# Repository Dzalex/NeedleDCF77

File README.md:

# NeedleDCF77
## General idea
This project is a clock that shows time using three analog meters (with needle) for hours, minutes and seconds, and a VFD for the date. The time reference is the [DCF77](https://en.wikipedia.org/wiki/DCF77) longwave signal, receivable across most of Europe — no manual time setting, no NTP, no RTC drift correction needed beyond the daily resync.

### Assembled clock

## Hardware
  - Main microcontroller: *STM32L051C8T6*
  - Power supply built around Analog Devices' *LTC3558* (Li-Po charge + regulation)
  - DCF77 receiver module: *EB6180B1COB77K5A1*
  - [VFD](https://en.wikipedia.org/wiki/Vacuum_fluorescent_display) for the date — a salvaged Itron FG95A
    - Driver: PT6312
    - Filament driver: LM4871 (alternative: LM9022)
    - Inverting regulator: LT1617
  - Analog meters, repurposed as needle displays:
    - Simpson 60 x 60 mm — hours
    - 85C1-A — minutes
    - 91C4 — seconds
  - Enclosure: wooden box, 20 x 10 x 6 cm
  - Battery: Panasonic 18650B

Schematic and PCB are designed in *KiCad* — see [`hardware/NeedleDCF77`](hardware/NeedleDCF77), including a rendered [schematic PDF](hardware/NeedleDCF77/DCF77Needle_schematic.pdf).

## Software
Firmware lives in [`sw/STM32CubeIDE_Project`](sw/STM32CubeIDE_Project), written in C on top of **FreeRTOS**, developed with **STM32CubeIDE** / STM32CubeMX and built with **CMake**.

### Layout
  - `Core/` — STM32CubeMX-generated init code, HAL configuration, and the FreeRTOS task wiring (`freertos.c`).
  - `BSP/` — hardware-facing drivers: DCF77 signal capture (`dcf77.c`), needle PWM output (`needle.c`), VFD control (`vfd.c`), battery/power management (`powerManagement.c`).
  - `App/` — hardware-independent application logic: DCF77 frame decoding (`dcf77Decoding.c`), needle/VFD interface state (`interface.c`).

### What it does
  - `StartDCF77Task` samples the DCF77 signal, decodes the time/date frame, validates it (parity + range/sanity checks) and syncs the RTC once per day (2 AM) or on button press.
  - `StartInterfaceTask` drives the needles from RTC time every second and shows the date on the VFD on button press; the display is suspended while a sync is in progress.
  - FreeRTOS tickless idle is enabled (`Core/Inc/FreeRTOSConfig.h`) so the MCU sleeps between scheduled work; `powerManagement.c` separately handles battery voltage readout and Li-Po charger control (LTC3558).

### Building the firmware
```sh
cmake --preset Debug      # or Release
cmake --build build/Debug
```
The project can also be opened directly in STM32CubeIDE.

### Running the unit tests
DCF77 frame decoding (`App/Src/dcf77Decoding.c`) is unit-tested on the host with [Unity](sw/STM32CubeIDE_Project/test/subprojects/unity), independent of any HAL/hardware dependency:
```sh
cd sw/STM32CubeIDE_Project/test
meson setup build
meson test -C build
```

## Improvements to come
  - Algorithm to index the current bit by time elapsed from the minute mark, so a missed/noisy pulse doesn't throw off subsequent bits, and to retain good bits from a previous sample.
  - Improve battery monitoring and charging. Alerting user on that regard.

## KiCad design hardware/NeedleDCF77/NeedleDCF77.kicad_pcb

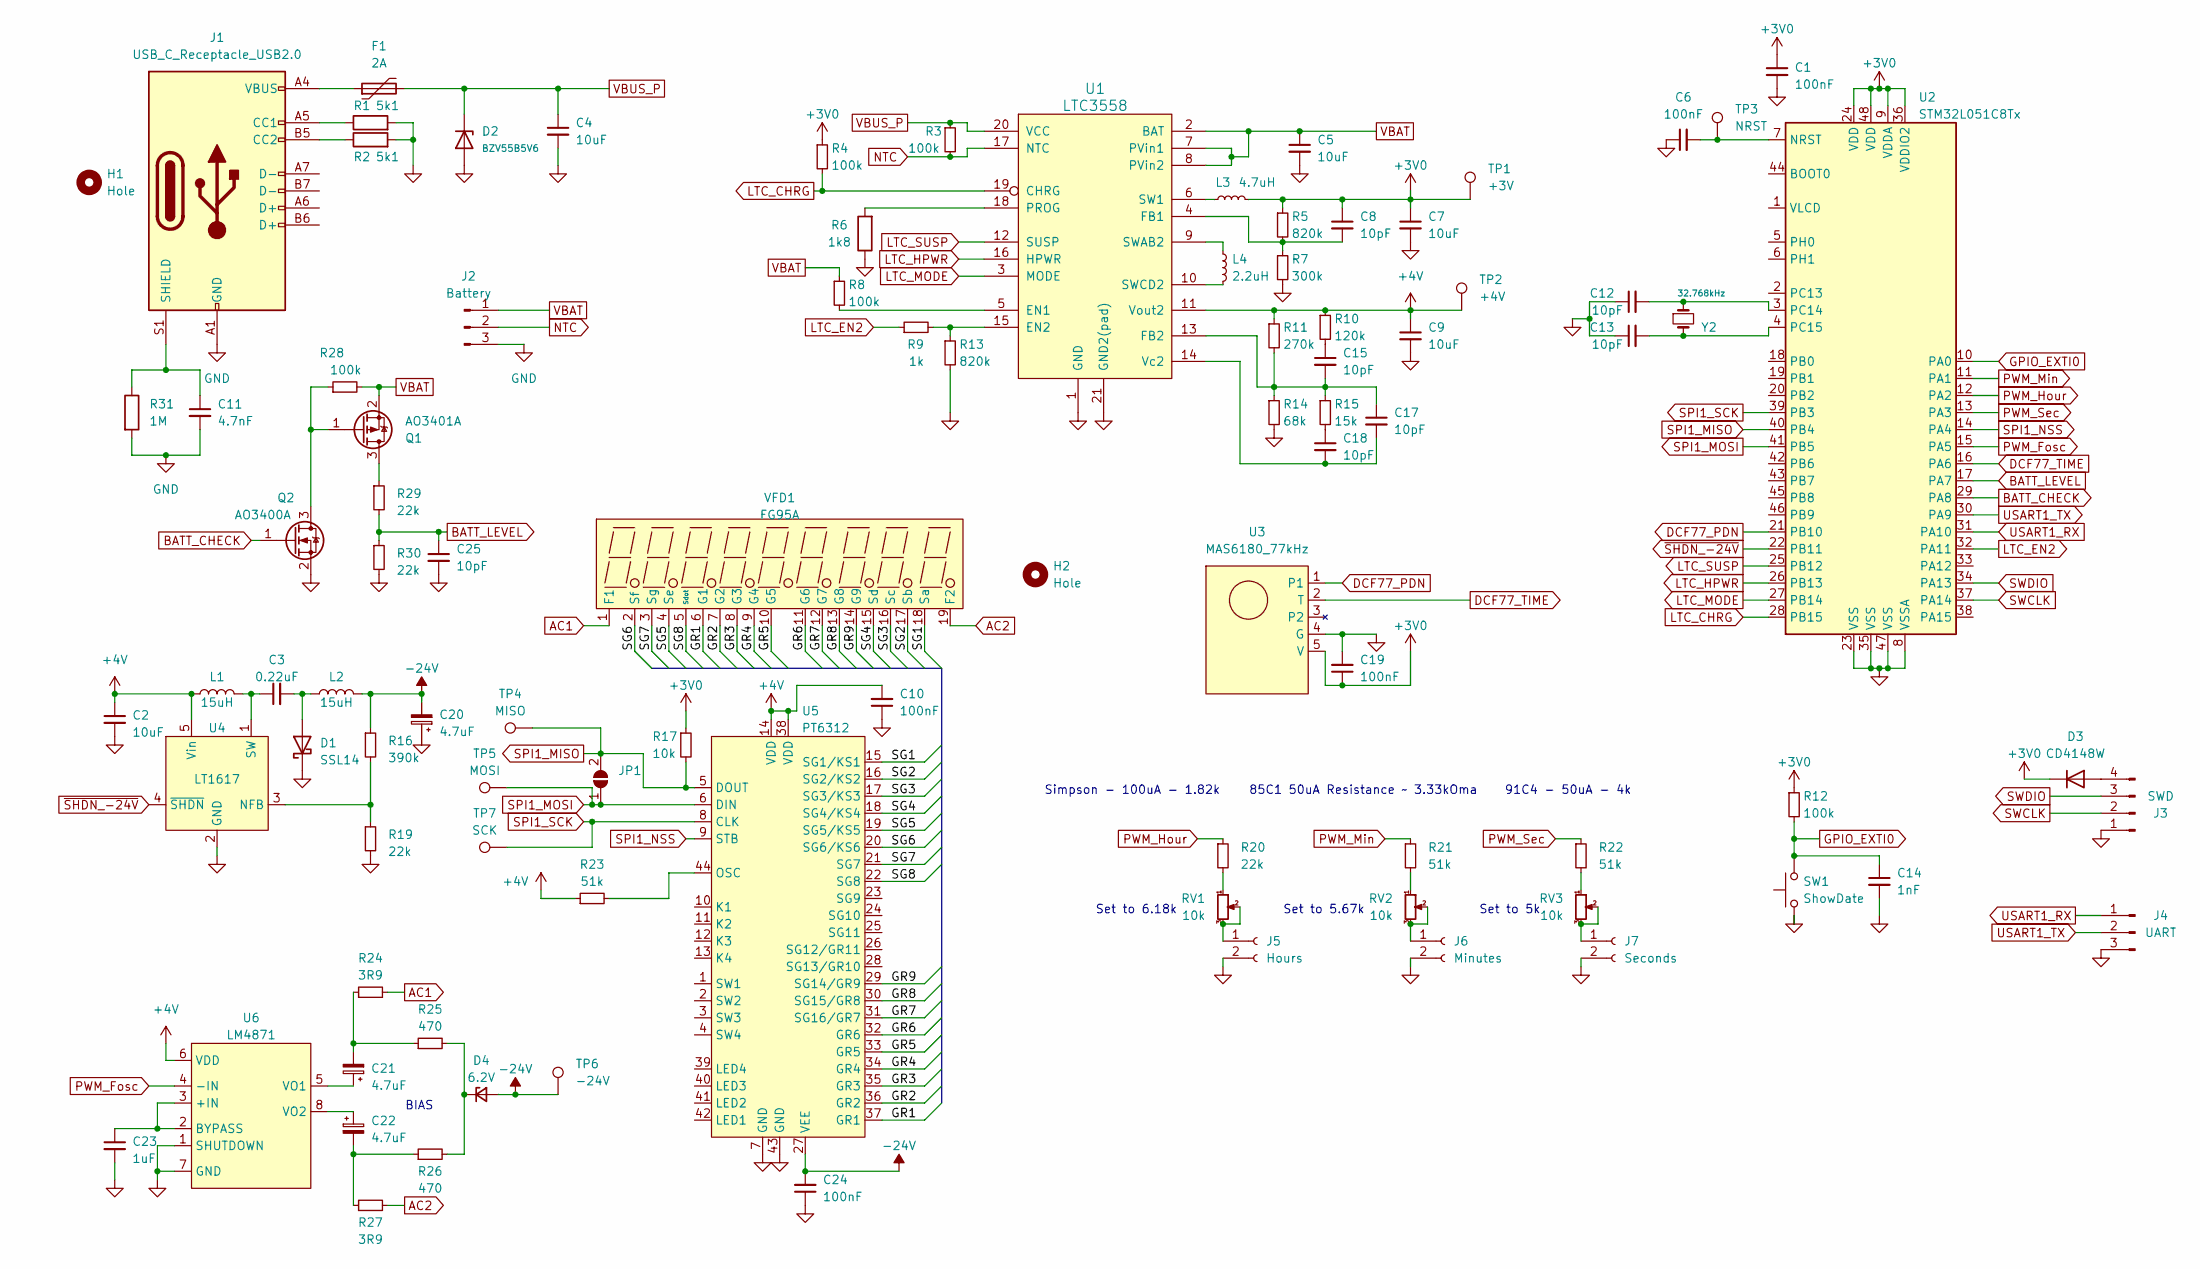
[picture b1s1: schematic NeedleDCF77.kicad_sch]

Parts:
C1, C6, C10, C19, C24: 100nF; C_0805_2012Metric_Pad1.18x1.45mm_HandSolder
C2, C4, C5, C7, C9: 10uF; C_1206_3216Metric_Pad1.33x1.80mm_HandSolder
C3: 0.22uF; C_1206_3216Metric_Pad1.33x1.80mm_HandSolder
C8, C12, C13, C15, C17, C18, C25: 10pF; C_0805_2012Metric_Pad1.18x1.45mm_HandSolder
C11: 4.7nF; C_1206_3216Metric_Pad1.33x1.80mm_HandSolder
C14: 1nF; C_1206_3216Metric_Pad1.33x1.80mm_HandSolder
C20: 4.7uF; CP_EIA-3528-21_Kemet-B_Pad1.50x2.35mm_HandSolder
C21, C22: 4.7uF; CP_Elec_4x5.7
C23: 1uF; C_0805_2012Metric_Pad1.18x1.45mm_HandSolder
D1: SSL14; D_SMA_Handsoldering
D2: BZV55B5V6; D_MiniMELF
D3: CD4148W; D_0805_2012Metric
D4: 6.2V; D_DO-35_SOD27_P2.54mm_Vertical_AnodeUp
F1: 2A; Fuse_2512_6332Metric_Pad1.52x3.35mm_HandSolder
H1, H2: Hole; MountingHole_3.2mm_M3_DIN965_Pad_TopBottom
J1: USB_C_Receptacle_USB2.0; Molex-2169890001-MFG
J2: Battery; Molex_KK-254_AE-6410-03A_1x03_P2.54mm_Vertical
J3: SWD; PinHeader_1x04_P2.54mm_Vertical
J4: UART; PinHeader_1x03_P2.54mm_Vertical
J5: Hours; Molex_KK-254_AE-6410-02A_1x02_P2.54mm_Vertical
J6: Minutes; Molex_KK-254_AE-6410-02A_1x02_P2.54mm_Vertical
J7: Seconds; Molex_KK-254_AE-6410-02A_1x02_P2.54mm_Vertical
JP1: SolderJumper-2_P1.3mm_Open_TrianglePad1.0x1.5mm
L1, L2: 15uH; L_12x12mm_H8mm
L3: 4.7uH; L_Ferrocore_DLG-0504
L4: 2.2uH; L_Ferrocore_DLG-0504
Q1: AO3401A; SOT-23
Q2: AO3400A; SOT-23
R1, R2: 5k1; R_0805_2012Metric_Pad1.20x1.40mm_HandSolder
R3, R4, R8, R12, R28: 100k; R_0805_2012Metric_Pad1.20x1.40mm_HandSolder
R5, R13: 820k; R_0805_2012Metric_Pad1.20x1.40mm_HandSolder
R6: 1k8; R_0805_2012Metric_Pad1.20x1.40mm_HandSolder
R7: 300k; R_0805_2012Metric_Pad1.20x1.40mm_HandSolder
R9: 1k; R_0805_2012Metric_Pad1.20x1.40mm_HandSolder
R10: 120k; R_1206_3216Metric_Pad1.30x1.75mm_HandSolder
R11: 270k; R_0805_2012Metric_Pad1.20x1.40mm_HandSolder
R14: 68k; R_Axial_DIN0207_L6.3mm_D2.5mm_P2.54mm_Vertical
R15: 15k; R_0805_2012Metric_Pad1.20x1.40mm_HandSolder
R16: 390k; R_0805_2012Metric_Pad1.20x1.40mm_HandSolder
R17: 10k; R_0805_2012Metric_Pad1.20x1.40mm_HandSolder
R19, R20, R29, R30: 22k; R_0805_2012Metric_Pad1.20x1.40mm_HandSolder
R21, R22, R23: 51k; R_0603_1608Metric_Pad0.98x0.95mm_HandSolder
R24, R27: 3R9; R_1206_3216Metric_Pad1.30x1.75mm_HandSolder
R25, R26: 470; R_0805_2012Metric_Pad1.20x1.40mm_HandSolder
R31: 1M; R_0805_2012Metric_Pad1.20x1.40mm_HandSolder
RV1, RV2, RV3: 10k; Potentiometer_Bourns_3296Y_Vertical
SW1: ShowDate; Molex_KK-254_AE-6410-02A_1x02_P2.54mm_Vertical
TP1: +3V; TestPoint_Pad_1.5x1.5mm
TP2: +4V; TestPoint_Pad_1.5x1.5mm
TP3: NRST; TestPoint_Pad_1.5x1.5mm
TP4: MISO; TestPoint_Pad_1.5x1.5mm
TP5: MOSI; TestPoint_Pad_1.5x1.5mm
TP6: -24V; TestPoint_Pad_1.5x1.5mm
TP7: SCK; TestPoint_Pad_1.5x1.5mm
U1: LTC3558; QFN-20-1EP_3x3mm_P0.4mm_EP1.65x1.65mm
U2: STM32L051C8Tx; LQFP-48_7x7mm_P0.5mm
U3: MAS6180_77kHz; MAS6180_module
U4: LT1617; SOT-23-5_HandSoldering
U5: PT6312; LQFP-44_10x10mm_P0.8mm
U6: LM4871; SOIC-8_3.9x4.9mm_P1.27mm
VFD1: FG95A
Y2: 32.768kHz; Crystal_C38-LF_D3.0mm_L8.0mm_Horizontal

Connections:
+3V0: C1.1, C7.1, C8.1, C19.1, D3.1 (K), L3.2, R4.1, R5.1, R12.1, R17.1, TP1.1, U2.9 (VDDA), U2.24 (VDD), U2.36 (VDDIO2), U2.48 (VDD), U3.5 (V)
+4V: C2.1, C9.1, C10.2, L1.1, R10.1, R11.1, R23.1, TP2.1, U1.11 (Vout2), U4.5 (Vin), U5.14 (VDD), U5.38 (VDD), U6.6 (VDD)
-24V: C20.2, C24.2, D4.2 (A), L2.2, R16.1, TP6.1, U5.27 (VEE)
/GR1: U5.37 (GR1), VFD1.6 (G1)
/GR2: U5.36 (GR2), VFD1.7 (G2)
/GR3: U5.35 (GR3), VFD1.8 (G3)
/GR4: U5.34 (GR4), VFD1.9 (G4)
/GR5: U5.33 (GR5), VFD1.10 (G5)
/GR6: U5.32 (GR6), VFD1.11 (G6)
/GR7: U5.31 (SG16/GR7), VFD1.12 (G7)
/GR8: U5.30 (SG15/GR8), VFD1.13 (G8)
/GR9: U5.29 (SG14/GR9), VFD1.14 (G9)
/SG1: U5.15 (SG1/KS1), VFD1.18 (Sa)
/SG2: U5.16 (SG2/KS2), VFD1.17 (Sb)
/SG3: U5.17 (SG3/KS3), VFD1.16 (Sc)
/SG4: U5.18 (SG4/KS4), VFD1.15 (Sd)
/SG5: U5.19 (SG5/KS5), VFD1.4 (Se)
/SG6: U5.20 (SG6/KS6), VFD1.2 (Sf)
/SG7: U5.21 (SG7), VFD1.3 (Sg)
/SG8: U5.22 (SG8), VFD1.5 (Sdot)
AC1: R24.2, VFD1.1 (F1)
AC2: R27.2, VFD1.19 (F2)
BATT_CHECK: Q2.1 (G), U2.29 (PA8)
BATT_LEVEL: C25.1, R29.2, R30.1, U2.17 (PA7)
DCF77_PDN: U2.21 (PB10), U3.1
DCF77_TIME: U2.16 (PA6), U3.2 (T)
GND: C1.2, C2.2, C4.2, C5.2, C6.1, C7.2, C9.2, C10.1, C11.2, C12.1, C13.1, C14.2, C19.2, C20.1, C23.2, C24.1, C25.2, D1.1 (K), D2.2 (A), J1.A1 (GND), J1.A12 (GND), J1.B1 (GND), J1.B12 (GND), J2.3, J3.1, J4.3, J5.2, J6.2, J7.2, Q2.2 (S), R1.2, R2.2, R6.1, R7.2, R13.2, R14.2, R19.2, R30.2, R31.2, SW1.1, U1.1 (GND), U1.21 (GND2(pad)), U2.8 (VSSA), U2.23 (VSS), U2.35 (VSS), U2.47 (VSS), U3.4 (G), U4.2 (GND), U5.7 (GND), U5.43 (GND), U6.1 (SHUTDOWN), U6.7 (GND)
GPIO_EXTI0: C14.1, R12.2, SW1.2, U2.10 (PA0)
LTC_CHRG: R4.2, U1.19 (CHRG), U2.28 (PB15)
LTC_EN2: R9.1, U2.32 (PA11)
LTC_HPWR: U1.16 (HPWR), U2.26 (PB13)
LTC_MODE: U1.3 (MODE), U2.27 (PB14)
LTC_SUSP: U1.12 (SUSP), U2.25 (PB12)
NTC: J2.2, R3.2, U1.17 (NTC)
unnamed: C15.1, R10.2
unnamed: C18.1, R15.2
unnamed: C21.2, R24.1, R25.1
unnamed: C22.2, R26.1, R27.1
unnamed: C3.2, D1.2 (A), L2.1
unnamed: D3.2 (A), J3.4
unnamed: D4.1 (K), R25.2, R26.2
unnamed: F1.1, J1.A4 (VBUS), J1.A9 (VBUS), J1.B4 (VBUS), J1.B9 (VBUS)
unnamed: J1.A5 (CC1), R1.1
unnamed: J1.B5 (CC2), R2.1
unnamed: C11.1, J1.S1 (SHIELD), R31.1
unnamed: J5.1, RV1.2, RV1.3
unnamed: J6.1, RV2.2, RV2.3
unnamed: J7.1, RV3.2, RV3.3
unnamed: Q1.3 (D), R29.1
unnamed: Q1.1 (G), Q2.3 (D), R28.1
unnamed: R20.2, RV1.1
unnamed: R21.2, RV2.1
unnamed: R22.2, RV3.1
unnamed: R8.2, U1.5 (EN1)
unnamed: R9.2, R13.1, U1.15 (EN2)
unnamed: C8.2, R5.2, R7.1, U1.4 (FB1)
unnamed: C15.2, C17.1, R11.2, R14.1, R15.1, U1.13 (FB2)
unnamed: R6.2, U1.18 (PROG)
unnamed: L3.1, U1.6 (SW1)
unnamed: L4.1, U1.9 (SWAB2)
unnamed: L4.2, U1.10 (SWCD2)
unnamed: C17.2, C18.2, U1.14 (Vc2)
unnamed: C6.2, TP3.1, U2.7 (NRST)
unnamed: C12.2, U2.3 (PC14), Y2.1
unnamed: C13.2, U2.4 (PC15), Y2.2
unnamed: R16.2, R19.1, U4.3 (NFB)
unnamed: C3.1, L1.2, U4.1 (SW)
unnamed: R23.2, U5.44 (OSC)
unnamed: C23.1, U6.2 (BYPASS), U6.3 (+IN)
unnamed: C21.1, U6.5 (VO1)
unnamed: C22.1, U6.8 (VO2)
PWM_Fosc: U2.15 (PA5), U6.4 (-IN)
PWM_Hour: R20.1, U2.12 (PA2)
PWM_Min: R21.1, U2.11 (PA1)
PWM_Sec: R22.1, U2.13 (PA3)
SPI1_MISO: JP1.2 (B), R17.2, TP4.1, U2.40 (PB4), U5.5 (DOUT)
SPI1_MOSI: JP1.1 (A), TP5.1, U2.41 (PB5), U5.6 (DIN)
SPI1_NSS: U2.14 (PA4), U5.9 (STB)
SPI1_SCK: TP7.1, U2.39 (PB3), U5.8 (CLK)
SWCLK: J3.2, U2.37 (PA14)
SWDIO: J3.3, U2.34 (PA13)
USART1_RX: J4.1, U2.31 (PA10)
USART1_TX: J4.2, U2.30 (PA9)
VBAT: C5.1, J2.1, Q1.2 (S), R8.1, R28.2, U1.2 (BAT), U1.7 (PVin1), U1.8 (PVin2)
VBUS_P: C4.1, D2.1 (K), F1.2, R3.1, U1.20 (VCC)
~SHDN_-24V: U2.22 (PB11), U4.4 (~SHDN)

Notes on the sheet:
91C4 - 50uA - 4k
Set to 5.67k
Set to 5k
Set to 6.18k
Simpson - 100uA - 1.82k
85C1 50uA Resistance ~ 3.33kOma
BIAS

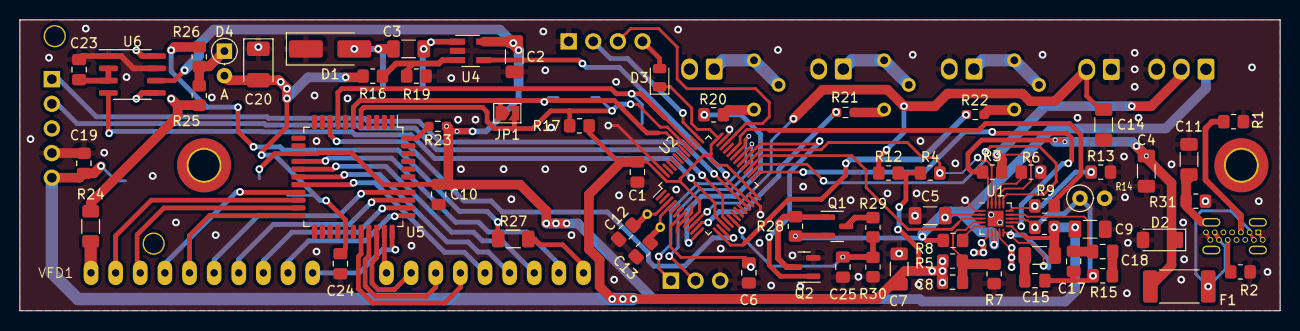
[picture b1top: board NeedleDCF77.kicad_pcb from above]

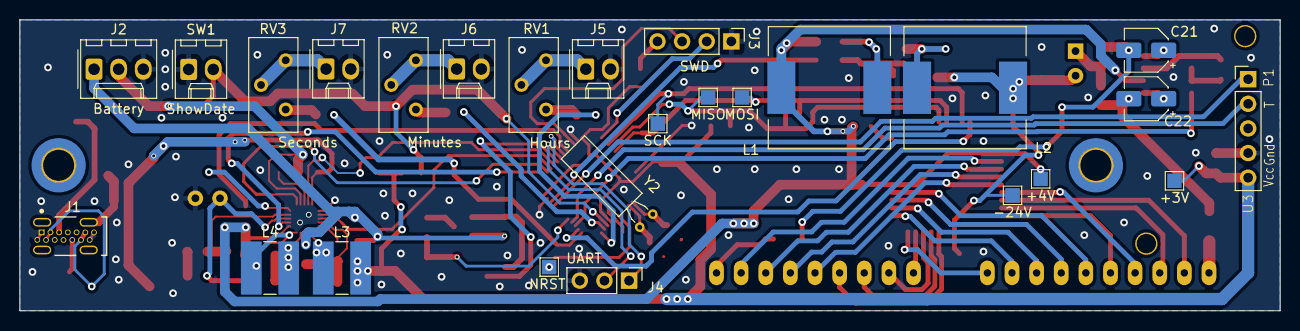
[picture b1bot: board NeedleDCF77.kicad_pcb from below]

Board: 2 copper layers, 130.0 x 30.0 mm, 94 parts (26 on the bottom side), 86 nets.

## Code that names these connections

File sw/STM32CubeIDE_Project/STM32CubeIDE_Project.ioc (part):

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Mcu.Name=STM32L051C(6-8)Tx
Mcu.Package=LQFP48
Mcu.UserName=STM32L051C8Tx
PA0.GPIOParameters=GPIO_ModeDefaultEXTI
PA0.GPIO_ModeDefaultEXTI=GPIO_MODE_IT_FALLING
PA0.Signal=GPXTI0
PA1.GPIOParameters=GPIO_Label
PA1.GPIO_Label=PWM_Min
PA1.Signal=S_TIM2_CH2
PA11.GPIOParameters=GPIO_Label
PA11.GPIO_Label=LTC_EN2
PA11.Signal=GPIO_Output
PA13.Mode=Serial_Wire
PA13.Signal=SYS_SWDIO
PA14.Mode=Serial_Wire
PA14.Signal=SYS_SWCLK
PA2.GPIOParameters=GPIO_Label
PA2.GPIO_Label=PWM_Hour
PA2.Signal=S_TIM2_CH3
PA3.GPIOParameters=GPIO_Label
PA3.GPIO_Label=PWM_Sec
PA3.Signal=S_TIM2_CH4
PA4.GPIOParameters=PinState,GPIO_Label
PA4.GPIO_Label=VFD_STB
PA4.PinState=GPIO_PIN_SET
PA4.Signal=GPIO_Output
PA5.GPIOParameters=GPIO_Label
PA5.GPIO_Label=PWM_FOSC
PA5.Signal=S_TIM2_CH1
PA6.Signal=S_TIM22_CH1
PA7.GPIOParameters=GPIO_Label
PA7.GPIO_Label=BATT_LEVEL
PA7.Mode=IN7
PA7.Signal=ADC_IN7
PA8.GPIOParameters=GPIO_Label
PA8.GPIO_Label=BATT_CHECK
PA8.Signal=GPIO_Output
PB10.GPIOParameters=PinState,GPIO_Label
PB10.GPIO_Label=DCF77_PDN
PB10.PinState=GPIO_PIN_SET
PB10.Signal=GPIO_Output
PB11.GPIOParameters=GPIO_Label
PB11.GPIO_Label=SHDN_24V
PB11.Signal=GPIO_Output
PB12.GPIOParameters=GPIO_Label
PB12.GPIO_Label=LTC_SUSP
PB12.Signal=GPIO_Output
PB13.GPIOParameters=GPIO_Label
PB13.GPIO_Label=LTC_HPWR
PB13.Signal=GPIO_Output
PB14.GPIOParameters=GPIO_Label
PB14.GPIO_Label=LTC_MODE
PB14.Signal=GPIO_Output
PB15.GPIOParameters=GPIO_PuPd,GPIO_Label
PB15.GPIO_Label=LTC_CHRG
PB15.GPIO_PuPd=GPIO_PULLUP
PB15.Signal=GPIO_Input
PB3.Mode=Full_Duplex_Master
PB3.Signal=SPI1_SCK
PB4.Mode=Full_Duplex_Master
PB4.Signal=SPI1_MISO
PB5.Mode=Full_Duplex_Master
PB5.Signal=SPI1_MOSI
PC14-OSC32_IN.Mode=LSE-External-Oscillator
PC14-OSC32_IN.Signal=RCC_OSC32_IN
PC15-OSC32_OUT.Mode=LSE-External-Oscillator
PC15-OSC32_OUT.Signal=RCC_OSC32_OUT
RCC.HSE_VALUE=8000000
RCC.SYSCLKFreq_VALUE=4194000
board=custom

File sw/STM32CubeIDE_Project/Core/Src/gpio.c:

/* USER CODE BEGIN Header */
/**
  ******************************************************************************
  * @file    gpio.c
  * @brief   This file provides code for the configuration
  *          of all used GPIO pins.
  ******************************************************************************
  * @attention
  *
  * Copyright (c) 2022 STMicroelectronics.
  * All rights reserved.
  *
  * This software is licensed under terms that can be found in the LICENSE file
  * in the root directory of this software component.
  * If no LICENSE file comes with this software, it is provided AS-IS.
  *
  ******************************************************************************
  */
/* USER CODE END Header */

/* Includes ------------------------------------------------------------------*/
#include "gpio.h"

/* USER CODE BEGIN 0 */

/* USER CODE END 0 */

/*----------------------------------------------------------------------------*/
/* Configure GPIO                                                             */
/*----------------------------------------------------------------------------*/
/* USER CODE BEGIN 1 */

/* USER CODE END 1 */

/** Configure pins as
        * Analog
        * Input
        * Output
        * EVENT_OUT
        * EXTI
        * Free pins are configured automatically as Analog (this feature is enabled through
        * the Code Generation settings)
*/
void MX_GPIO_Init(void)
{

  GPIO_InitTypeDef GPIO_InitStruct = {0};

  /* GPIO Ports Clock Enable */
  __HAL_RCC_GPIOC_CLK_ENABLE();
  __HAL_RCC_GPIOH_CLK_ENABLE();
  __HAL_RCC_GPIOA_CLK_ENABLE();
  __HAL_RCC_GPIOB_CLK_ENABLE();

  /*Configure GPIO pin Output Level */
  HAL_GPIO_WritePin(VFD_STB_GPIO_Port, VFD_STB_Pin, GPIO_PIN_SET);

  /*Configure GPIO pin Output Level */
  HAL_GPIO_WritePin(DCF77_PDN_GPIO_Port, DCF77_PDN_Pin, GPIO_PIN_SET);

  /*Configure GPIO pin Output Level */
  HAL_GPIO_WritePin(GPIOB, SHDN_24V_Pin|LTC_SUSP_Pin|LTC_HPWR_Pin|LTC_MODE_Pin, GPIO_PIN_RESET);

  /*Configure GPIO pin Output Level */
  HAL_GPIO_WritePin(GPIOA, BATT_CHECK_Pin|LTC_EN2_Pin, GPIO_PIN_RESET);

  /*Configure GPIO pin : PC13 */
  GPIO_InitStruct.Pin = GPIO_PIN_13;
  GPIO_InitStruct.Mode = GPIO_MODE_ANALOG;
  GPIO_InitStruct.Pull = GPIO_NOPULL;
  HAL_GPIO_Init(GPIOC, &GPIO_InitStruct);

  /*Configure GPIO pins : PH0 PH1 */
  GPIO_InitStruct.Pin = GPIO_PIN_0|GPIO_PIN_1;
  GPIO_InitStruct.Mode = GPIO_MODE_ANALOG;
  GPIO_InitStruct.Pull = GPIO_NOPULL;
  HAL_GPIO_Init(GPIOH, &GPIO_InitStruct);

  /*Configure GPIO pin : PA0 */
  GPIO_InitStruct.Pin = GPIO_PIN_0;
  GPIO_InitStruct.Mode = GPIO_MODE_IT_FALLING;
  GPIO_InitStruct.Pull = GPIO_NOPULL;
  HAL_GPIO_Init(GPIOA, &GPIO_InitStruct);

  /*Configure GPIO pins : VFD_STB_Pin BATT_CHECK_Pin LTC_EN2_Pin */
  GPIO_InitStruct.Pin = VFD_STB_Pin|BATT_CHECK_Pin|LTC_EN2_Pin;
  GPIO_InitStruct.Mode = GPIO_MODE_OUTPUT_PP;
  GPIO_InitStruct.Pull = GPIO_NOPULL;
  GPIO_InitStruct.Speed = GPIO_SPEED_FREQ_LOW;
  HAL_GPIO_Init(GPIOA, &GPIO_InitStruct);

  /*Configure GPIO pins : PB0 PB1 PB2 PB6
                           PB7 PB8 PB9 */
  GPIO_InitStruct.Pin = GPIO_PIN_0|GPIO_PIN_1|GPIO_PIN_2|GPIO_PIN_6
                          |GPIO_PIN_7|GPIO_PIN_8|GPIO_PIN_9;
  GPIO_InitStruct.Mode = GPIO_MODE_ANALOG;
  GPIO_InitStruct.Pull = GPIO_NOPULL;
  HAL_GPIO_Init(GPIOB, &GPIO_InitStruct);

  /*Configure GPIO pins : DCF77_PDN_Pin SHDN_24V_Pin LTC_SUSP_Pin LTC_HPWR_Pin
                           LTC_MODE_Pin */
  GPIO_InitStruct.Pin = DCF77_PDN_Pin|SHDN_24V_Pin|LTC_SUSP_Pin|LTC_HPWR_Pin
                          |LTC_MODE_Pin;
  GPIO_InitStruct.Mode = GPIO_MODE_OUTPUT_PP;
  GPIO_InitStruct.Pull = GPIO_NOPULL;
  GPIO_InitStruct.Speed = GPIO_SPEED_FREQ_LOW;
  HAL_GPIO_Init(GPIOB, &GPIO_InitStruct);

  /*Configure GPIO pin : LTC_CHRG_Pin */
  GPIO_InitStruct.Pin = LTC_CHRG_Pin;
  GPIO_InitStruct.Mode = GPIO_MODE_INPUT;
  GPIO_InitStruct.Pull = GPIO_PULLUP;
  HAL_GPIO_Init(LTC_CHRG_GPIO_Port, &GPIO_InitStruct);

  /*Configure GPIO pins : PA9 PA10 PA12 PA15 */
  GPIO_InitStruct.Pin = GPIO_PIN_9|GPIO_PIN_10|GPIO_PIN_12|GPIO_PIN_15;
  GPIO_InitStruct.Mode = GPIO_MODE_ANALOG;
  GPIO_InitStruct.Pull = GPIO_NOPULL;
  HAL_GPIO_Init(GPIOA, &GPIO_InitStruct);

  /* EXTI interrupt init*/
  HAL_NVIC_SetPriority(EXTI0_1_IRQn, 3, 0);
  HAL_NVIC_EnableIRQ(EXTI0_1_IRQn);

}

/* USER CODE BEGIN 2 */

/* USER CODE END 2 */

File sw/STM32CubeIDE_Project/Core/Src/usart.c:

/* USER CODE BEGIN Header */
/**
  ******************************************************************************
  * @file    usart.c
  * @brief   This file provides code for the configuration
  *          of the USART instances.
  ******************************************************************************
  * @attention
  *
  * Copyright (c) 2022 STMicroelectronics.
  * All rights reserved.
  *
  * This software is licensed under terms that can be found in the LICENSE file
  * in the root directory of this software component.
  * If no LICENSE file comes with this software, it is provided AS-IS.
  *
  ******************************************************************************
  */
/* USER CODE END Header */
/* Includes ------------------------------------------------------------------*/
#include "usart.h"

/* USER CODE BEGIN 0 */

/* USER CODE END 0 */

UART_HandleTypeDef huart1;

/* USART1 init function */

void MX_USART1_UART_Init(void)
{

  /* USER CODE BEGIN USART1_Init 0 */

  /* USER CODE END USART1_Init 0 */

  /* USER CODE BEGIN USART1_Init 1 */

  /* USER CODE END USART1_Init 1 */
  huart1.Instance = USART1;
  huart1.Init.BaudRate = 115200;
  huart1.Init.WordLength = UART_WORDLENGTH_8B;
  huart1.Init.StopBits = UART_STOPBITS_1;
  huart1.Init.Parity = UART_PARITY_NONE;
  huart1.Init.Mode = UART_MODE_TX_RX;
  huart1.Init.HwFlowCtl = UART_HWCONTROL_NONE;
  huart1.Init.OverSampling = UART_OVERSAMPLING_16;
  huart1.Init.OneBitSampling = UART_ONE_BIT_SAMPLE_DISABLE;
  huart1.AdvancedInit.AdvFeatureInit = UART_ADVFEATURE_NO_INIT;
  if (HAL_UART_Init(&huart1) != HAL_OK)
  {
    Error_Handler();
  }
  /* USER CODE BEGIN USART1_Init 2 */

  /* USER CODE END USART1_Init 2 */

}

void HAL_UART_MspInit(UART_HandleTypeDef* uartHandle)
{

  GPIO_InitTypeDef GPIO_InitStruct = {0};
  if(uartHandle->Instance==USART1)
  {
  /* USER CODE BEGIN USART1_MspInit 0 */

  /* USER CODE END USART1_MspInit 0 */
    /* USART1 clock enable */
    __HAL_RCC_USART1_CLK_ENABLE();

    __HAL_RCC_GPIOA_CLK_ENABLE();
    /**USART1 GPIO Configuration
    PA9     ------> USART1_TX
    PA10     ------> USART1_RX
    */
    GPIO_InitStruct.Pin = GPIO_PIN_9|GPIO_PIN_10;
    GPIO_InitStruct.Mode = GPIO_MODE_AF_PP;
    GPIO_InitStruct.Pull = GPIO_NOPULL;
    GPIO_InitStruct.Speed = GPIO_SPEED_FREQ_VERY_HIGH;
    GPIO_InitStruct.Alternate = GPIO_AF4_USART1;
    HAL_GPIO_Init(GPIOA, &GPIO_InitStruct);

  /* USER CODE BEGIN USART1_MspInit 1 */

  /* USER CODE END USART1_MspInit 1 */
  }
}

void HAL_UART_MspDeInit(UART_HandleTypeDef* uartHandle)
{

  if(uartHandle->Instance==USART1)
  {
  /* USER CODE BEGIN USART1_MspDeInit 0 */

  /* USER CODE END USART1_MspDeInit 0 */
    /* Peripheral clock disable */
    __HAL_RCC_USART1_CLK_DISABLE();

    /**USART1 GPIO Configuration
    PA9     ------> USART1_TX
    PA10     ------> USART1_RX
    */
    HAL_GPIO_DeInit(GPIOA, GPIO_PIN_9|GPIO_PIN_10);

  /* USER CODE BEGIN USART1_MspDeInit 1 */

  /* USER CODE END USART1_MspDeInit 1 */
  }
}

/* USER CODE BEGIN 1 */

/* USER CODE END 1 */

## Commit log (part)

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2022-03-27 Create hardware project (KiCad project)
2022-03-27 Add .zip ignore for KiCad
2022-03-27 First schematic save
2022-03-27 Repair gitignore
2022-03-28 Create footprint for MINI-M4
2022-03-28 Add MINI-M4 to schematic
2022-03-28 Init PCB
2022-04-01 Add library with LTC3558 and add it to schematic
2022-04-16 Edit LTC3558 dimensions
2022-08-17 Add doc folder and files provided by module seller
2022-08-17 Update README, General info test
2022-08-17 Initial reasonable README
2022-08-28 Create STM32Cube project with freeRtos and CMSISv2 API
    Check if it is possible to not use CMSIS...
2022-09-01 Add log of DCF77 signal
2022-09-04 Change MCU poroposal in README
2022-09-08 Change main MCU to STM32L051
2022-09-19 Add LTC3558 datasheet
2022-09-19 Implementation of 3V
2022-09-20 Discard F4 Cube project
2022-09-20 Create empty project for STM32L051C8T6
2022-09-20 Start configuring MCU
2022-09-25 Add new DCF samples log
2022-10-16 Generate first STM Cube code
2022-11-26 Initial analysis with matching filter. Not working.
2022-12-06 Arduino sampler to get DCF77 samples
2022-12-06 Unknown changes in schematic - forget to commit
2022-12-06 Create symbol for PT6312 and add it to schematic
2022-12-06 Update page setup
2022-12-06 Split peripherals in multiple .h/.c files for readability
2022-12-06 Lower TOTAL_HEAP_SIZE to be able just to build
2022-12-07 Migration to MXCube 6.7.0
2022-12-07 Add DCF77, needle and VFD tasks
2022-12-07 Setup printf
2022-12-08 Change position of PWM pins
2022-12-08 Reduce stack size to be able to use NewLib Reentrant
2022-12-09 Update schematic IC symbol background
2023-02-19 Tweak convolution analysis (not working). Added a useful paper to docs.
2023-02-19 Move to KiCad 7.0
2023-03-10 Update MxCube and FW package
2023-03-10 Ignore cyclo file
2023-03-10 Chose correct pins for PWM
2023-03-10 Chose correct pins for SPI1
2023-03-10 Chose correct pins for UART1
2023-03-10 Update pins corrections in CubeMX
2023-03-20 Add ground to PT6312
2023-04-14 Create Symbol for LM4871 and add it to schematic
2023-04-16 Update README about VFD details
2023-04-19 Create VFD (FG95A) symbol and Footprint
2023-04-30 Create LT1617 library
2023-05-01 Create -24V power supply
2023-05-01 Implement VFD circuit
2023-05-01 Implement 5V for VFD circuitry
2023-05-01 Migration to MXCube 6.8.1
2023-07-03 Change positions of schematic components
2023-07-03 Change WKUP to EXTI0, so we are unable to get out of LowPower modes, no STOP
2023-07-03 Add debug interfaces
2023-07-03 Connect LTC3558 logic to MCU
2023-07-03 Connect LT1617 shutdown to MCU
2023-07-03 Name Fosc signal correctly
2023-07-05 Add DCF77 receiver module
2023-07-07 Connect DCF77 module to MCU
2023-07-07 Add push button for date show
2023-07-08 Add footprints and supplier codes - AMEND TO THIS
2023-07-08 Add new symbol to 32khz crystal so we can access ground
2023-07-08 Import changes to PCB
2023-08-06 Add battery measurement circuit and generate ADC code
2023-08-06 Update gitignore to ignore lck files
2023-08-21 Change Silk to Fab of dimesnion FG95A and DCF77 module
2023-08-21 Bulk work - working on layout
2023-08-21 Use HSI instead of HSE
2023-08-30 Add new USB C connector, flag type, Molex
2023-08-30 Initial version of PCB placement and routing
2023-09-02 Add test points to schematic and board
2023-09-02 Minor improvements regarding coupling and silkscreen
2023-09-24 Fix points from Nikola's review + add logo
2023-09-28 Final improvements
2023-09-28 Generate production files
2023-09-28 Fix pin naming
2023-09-28 Migrate MXCube, and make it build
2023-10-28 Add notes from Nikola
2023-10-28 Configure GPIO initial state
2023-10-28 Configure initial settings for freeRTOS
2023-10-28 Implement basic needle operations with PWM
2023-10-28 Test needle moving
2023-11-07 Some changes to .project configuration
2023-11-07 Change VDD to 3V
2023-11-07 Use RTC_TimeTypeDef as argument in time setting
2023-11-07 Implement power management for LTC
2023-11-08 Fix needle Set functions
2023-11-08 Implement first version on battery charging check
2023-11-09 Save Debug configuration for OpecOCD
2023-11-19 Refactor needle
2023-11-19 Make first settings to RTC
2023-11-19 Enable RTC WakeUp option and enable interrupt for wake up
2023-11-19 Fix needle position for 12AM/PM
2023-11-20 Implement first interrupt/event based clock with task interface
2023-11-20 Enable TICKLESS_IDLE in project
2023-11-20 Burst mode activated - save around 1mA
2023-11-20 Lower frequency to 4MHz, save 1.3mA
2023-11-22 Configure regulator voltage range 3 - save 0.4mA - NOW 2.2mA
2023-11-22 Use MSI as main clock, disable power hungry PLL - save 0.4mA - Now 1.8mA
2023-11-22 Activate SLEEP, we have to suspend task
2023-11-22 Use burst mode as main power mode - 1mA
2023-11-22 Use MSI clock @ 4194kHz as main clock; this disables PLL and HSI which are power hungry - > 1mA
2023-11-22 Set internal regulator to voltage range 3 - 0.3mA
2023-11-22 Suspend currently unused thread
2023-11-23 Set all free pins as analog - optimize power consumption
2023-11-26 Define VFD commands 1 and 2
2023-11-28 Add Command 3 and Command 4 and signature of initialisation function
2023-12-03 Add first font with numbers
2023-12-03 Add Pulse value for PWM channel 1 - Fosc for VFD
2023-12-03 Implement command function for VFD
2023-12-03 Implement VFD clear
2023-12-03 Implement VFD initialization function
2023-12-10 Speed up PWM frequency so we can heat up
2023-12-10 Lower the speed of VFD transmission
2023-12-10 Prepare for testing
2023-12-14 Fix font
2023-12-14 Use GPIO as Strobe instead of NSS option of SPI
2023-12-14 Fix VFD_Command, Implement strobe functions and fix clear
2023-12-14 Fix test
2023-12-15 Add 11dig 11seg command
2023-12-15 Activate and deactivate strobe forward declaration
2023-12-15 Activate SPI before sending any command
2023-12-15 Refactor position of constants for VFD
2023-12-16 Add font for letter and dot position
2023-12-16 Implement single character write to position with helper write function
2023-12-16 End strobe when clearing display
2023-12-16 Add brights constant and use it
2023-12-16 Export PrintCharacterAtPosition
2023-12-16 Fix Fixed address and test mode constants
2023-12-16 Fix digit 9 font
2023-12-16 Implement printing digit to position
2023-12-16 Implement Show date function
2023-12-16 Forward declaration of AdressSettingCommand
2023-12-19 Use 1kHz as PWM frequency.
    VFD is lit, and needles are moving correctly at this frequency
2023-12-19 Fix WriteDataToDisplay for data larger that 1
2023-12-19 Implement PowerOffAnd desalinization of VFD
2023-12-19 Magic number refactoring
2023-12-23 Refactoring step for cleaner interface #1
2023-12-23 Export showDate to interface
2023-12-23 Do not expose internal VFD constants
2023-12-23 Improve test function
2024-01-01 Index first digit as 0, so we can't have position 9
2024-01-01 Fix century comment
2024-01-01 Implement VFD library and provide function to show Date (#9)
    * Set SPI for communication with PT6312
    * Define VFD commands 1 and 2
    * Add Command 3 and Command 4 and signature of initialisation function
    * Add first font with numbers
    * Add Pulse value for PWM channel 1 - Fosc for VFD
    * Implement command function for VFD
2024-01-02 Create new timer for periodic checking of button - if it is active multiple times it is being held
2024-01-02 Detect falling edge of button signal
2024-01-02 Enable showing of date on button press
2024-01-02 Only INTERFACE_SECOND_FLAG was able to Unblock a task, all flags can unblock on wait
2024-01-02 Refactor naming for OS timer
2024-01-02 Add timer to turn of VFD
2024-01-02 Start timer and deinit VFD at timer callback
2024-01-02 Start periodic Timer and create callback that will check for button hold
2024-01-02 Refactor cyclic timer callback
2024-01-02 Increase task stack size to 128 words, before we had lower than 15 while running
2024-01-04 Stop cyclic timer after 3 seconds
2024-01-04 Support button to display date and start synch (#10)
    * Create new timer for periodic checking of button - if it is active multiple times it is being held
    * Detect falling edge of button signal
    * Enable showing of date on button press
    * Only INTERFACE_SECOND_FLAG was able to Unblock a task, all flags can unblock on wait
    * Refactor naming for OS timer
    * Add timer to turn of VFD
2024-01-04 Implement PrintPositiveNumber so we can show number on VFD
2024-01-05 Implement battery voltage get function with helper functions to enable its readout
2024-01-07 Enable TIM22 global interrupt
2024-01-20 Add dcf.h and enabling of receiver
2024-01-23 Use TIM22 as PWM input on IC1 pin, IC2 register secondary
2024-01-23 Refactor dcf77 with addition of timer start and stop functions
2024-01-23 Add message queue for DCF77 samples received by tim22 ISR
2024-01-23 Add ISR callback function for DCF77 timer input capture
2024-01-23 Example of how to use DCF77 Message queue of time samples
2024-01-23 Implemet time pulse sampling for DCF77 (#11)
    * Use TIM22 for DCF77 time signal input capture measuring
    Prescaler to get 1ms resolution
    Capture on both edges
    Filter noise with 5
    * Enable TIM22 global interrupt
    * Add dcf.h and enabling of receiver
2024-01-28 Add clock image to readme
2024-01-28 Add calibration value to RTC using LL driver
    Calculated CALM value using https://gist.github.com/esynr3z/8284f6dc10feab1e00609f26e42b974c
2024-01-28 Enable ADC LowPowerAutoWait and LowPowerAutoPowerOff
2024-01-28 Add initial constants
2024-01-28 Add dcf77 buffer
2024-01-28 Check what pulse we received
2024-01-28 Use union for DCF77 buffer
2024-01-28 Implement function that will fill buffer on specific location
2024-01-28 Add timeout constant
2024-01-28 Remove global struct
2024-06-22 Export data diagnostic function so we can test and use them
2024-09-09 Extract decoding functionality to improve testing and modularity
2024-09-09 Configure unity test framework with meson build
2024-09-09 Test IsFirstBitOne and repair issues found by test
2024-09-09 Migrate MXCube 6.12.0
2024-09-10 Test Encoding bit check function and Parity functions
2024-09-10 Finish implementation of CheckBuffer integrity and refactor DCF77_SetBufferBitOnPosition
2024-09-10 Enable optimisation to -O3, to test memory usage
2024-09-10 Test and fix CheckPulseType function
2024-09-10 Implement and test DecodeTimeToRTCTimeBuffer
2024-09-11 Implement and test DecodeDateToRTCDateBuffer
2024-09-11 Improve GetTimeAndDate
2024-09-11 Add Resume of DCF77 Task in state machine
2024-09-11 Change time minute before 2AM and fix hour decoding
2024-09-17 Fix preemption of task by allowing 10ms timeout on queue and fix button hold
2024-09-17 On GetTimeAndDate success set Time and set Date
2024-09-24 Timer changes: Add alarm for 2AM and configure inverted PWM input trigger slopes
2024-09-24 Change logic behind pulse length
2024-09-24 Re-enable cyclomatic complexity
2024-09-24 Put interrupt Callback functions to correct places
2024-09-24 Create event on 2AM alarm
2024-09-24 Fix logic inside GetTimeAndDate
2024-09-24 Fixup unsigned long to unsigned long long
2024-09-24 When there is a MINUTE PULSE we already have 0 on zero position, so move on next bit
2024-09-24 Fix alarm only to trigger at 2AM,not every other second during 2AM
2024-09-24 Fix pointer problem with time and date structure for decoding
2024-09-30 Better comment for minute mark in check Pulse
2024-09-30 Refactor parity check
2024-09-30 Refactor Time and Date decoding
2024-10-01 Add SampleTimeIsInRange and refactor CheckPulseType
2024-10-01 Add DCF77_ResetBuffer and refactor GetTimeAndDate
2024-10-02 Suppress noise by switching to Pulse Skip mode for switching regulator
2024-10-29 Initial implementation and usage of DCF77 signal decoding (#12)
    * Add initial constants
    * Add dcf77 buffer
    * Check what pulse we received
    * Use union for DCF77 buffer
    * Implement function that will fill buffer on specific location
    * Add timeout constant
2024-10-29 Remove usage of debug UART
2024-11-03 Add Run configuration for Release
2024-12-12 Update KiCad project
2025-04-06 Enable USE_TICKLESS_IDLE
2025-12-14 Update KiCad version of project
